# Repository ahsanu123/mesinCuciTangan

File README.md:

# Projek Dadakan - Mesin Cuci Tangan

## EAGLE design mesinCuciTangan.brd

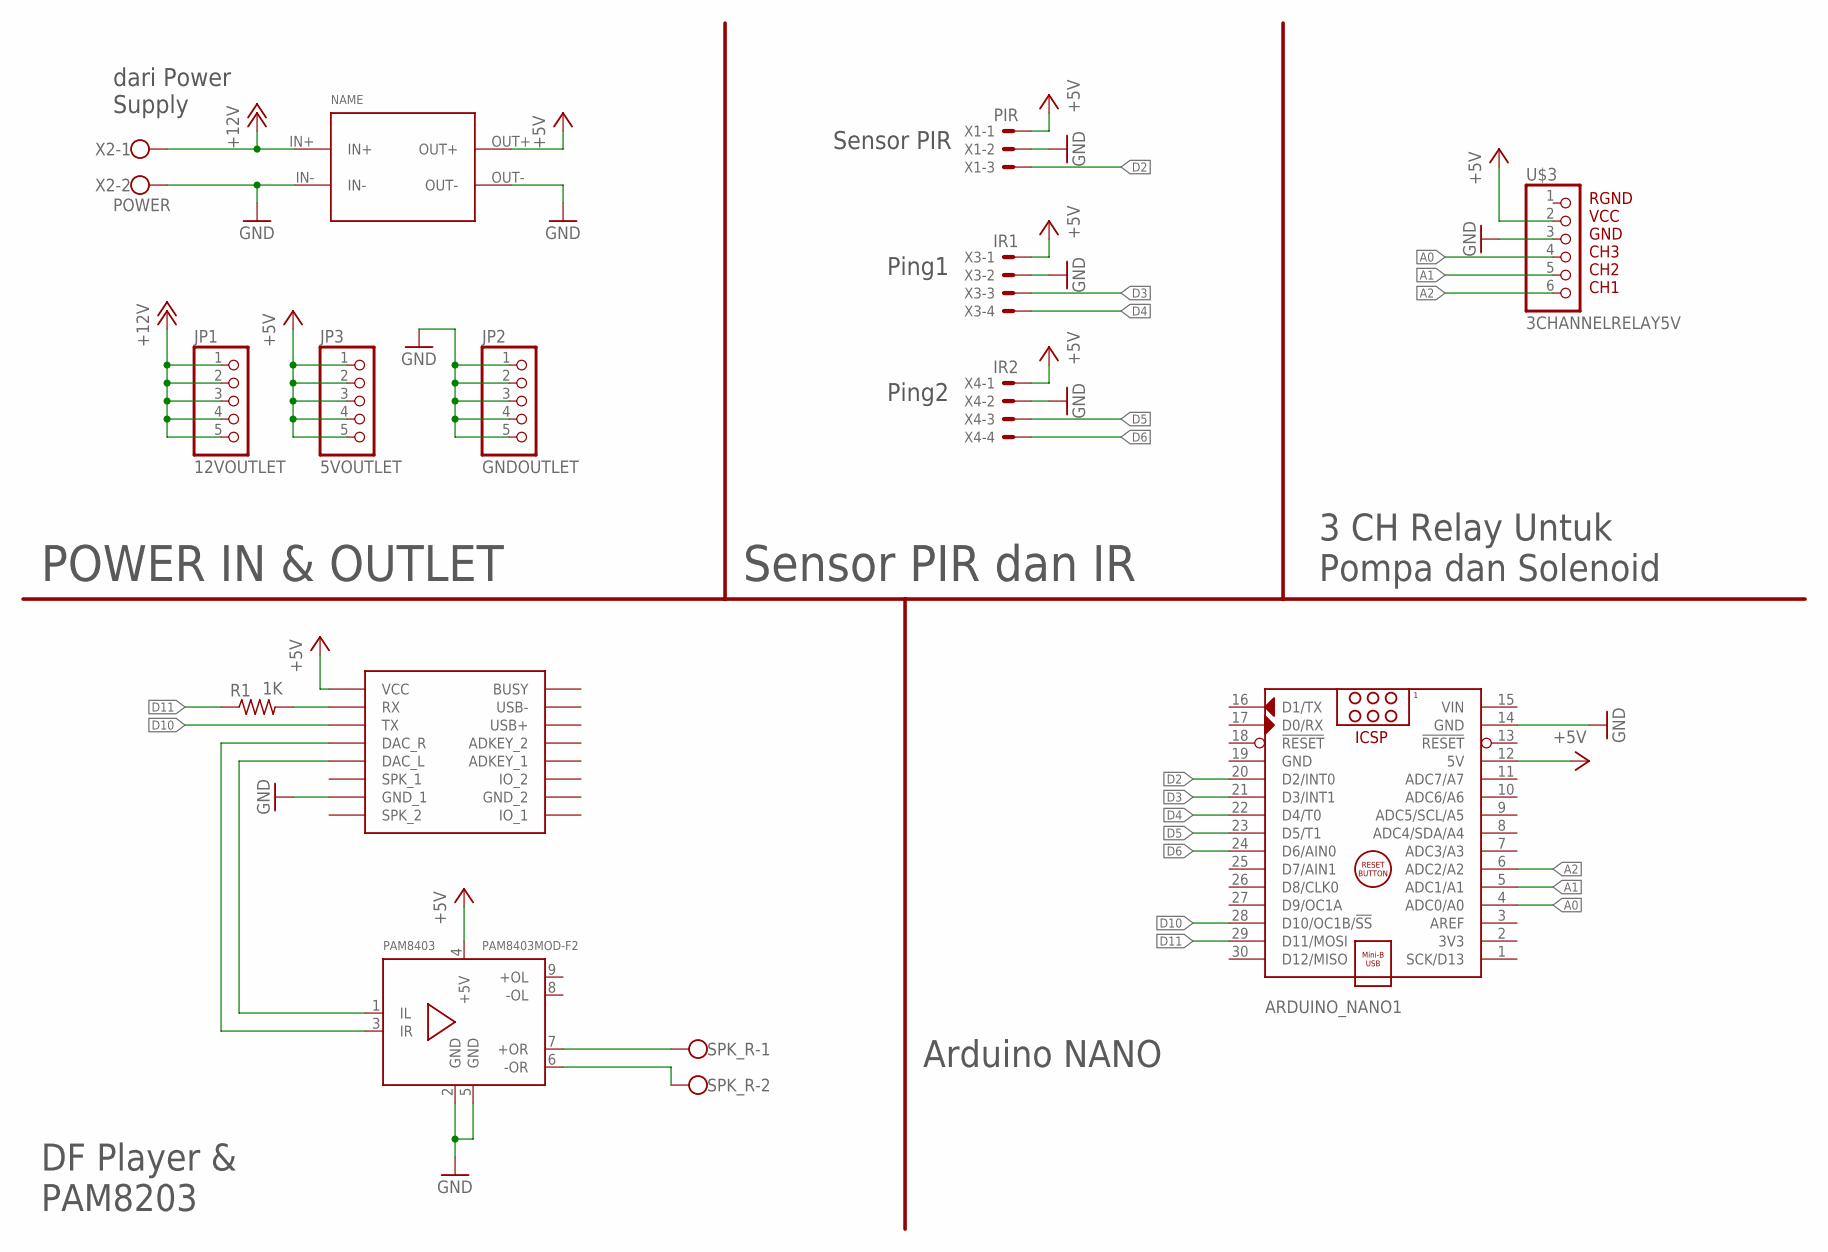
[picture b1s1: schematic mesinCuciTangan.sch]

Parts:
ARDUINO_NANO1: ARDUINO_NANO
JP1: 12VOUTLET; 1X05
JP2: GNDOUTLET; 1X05
JP3: 5VOUTLET; 1X05
LM2596: LM2596; CP8-ADJ
PAM8403: PAM8403MOD-F2; PAM8403MOD2
R1: 1K; 0207/10
SPK_R: W237-102
U$2: DFPLAYER
U$3: 3CHANNELRELAY5V; 3CHANNELRELAY
X1: PIR; 22-23-2031
X2: POWER; W237-102
X3: IR1; 22-23-2041
X4: IR2; 22-23-2041

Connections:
+5V: ARDUINO_NANO1.12 (5V), JP3.1, JP3.2, JP3.3, JP3.4, JP3.5, LM2596.OUT+, PAM8403.4 (+5V), U$2.VCC, U$3.2, X1.1, X3.1, X4.1
+12V: JP1.1, JP1.2, JP1.3, JP1.4, JP1.5, LM2596.IN+, X2.1
A0: ARDUINO_NANO1.4 (ADC0/A0), U$3.4
A1: ARDUINO_NANO1.5 (ADC1/A1), U$3.5
A2: ARDUINO_NANO1.6 (ADC2/A2), U$3.6
D2: ARDUINO_NANO1.20 (D2/INT0), X1.3
D3: ARDUINO_NANO1.21 (D3/INT1), X3.3
D4: ARDUINO_NANO1.22 (D4/T0), X3.4
D5: ARDUINO_NANO1.23 (D5/T1), X4.3
D6: ARDUINO_NANO1.24 (D6/AIN0), X4.4
D10: ARDUINO_NANO1.28 (D10/OC1B/!SS), U$2.TX
D11: ARDUINO_NANO1.29 (D11/MOSI), R1.1
GND: ARDUINO_NANO1.14 (GND), ARDUINO_NANO1.19 (GND), JP2.1, JP2.2, JP2.3, JP2.4, JP2.5, LM2596.IN-, LM2596.OUT-, PAM8403.2 (GND), PAM8403.5 (GND), U$2.GND_1, U$3.3, X1.2, X2.2, X3.2, X4.2
unnamed: PAM8403.7 (+OR), SPK_R.1
unnamed: PAM8403.1 (IL), U$2.DAC_L
unnamed: PAM8403.3 (IR), U$2.DAC_R
unnamed: PAM8403.6 (-OR), SPK_R.2
unnamed: R1.2, U$2.RX
VIN: ARDUINO_NANO1.15 (VIN)

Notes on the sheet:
dari Power Supply
Sensor PIR
Ping1
Ping2
POWER IN & OUTLET
Sensor PIR dan IR
3 CH Relay Untuk Pompa dan Solenoid
DF Player & PAM8203
Arduino NANO

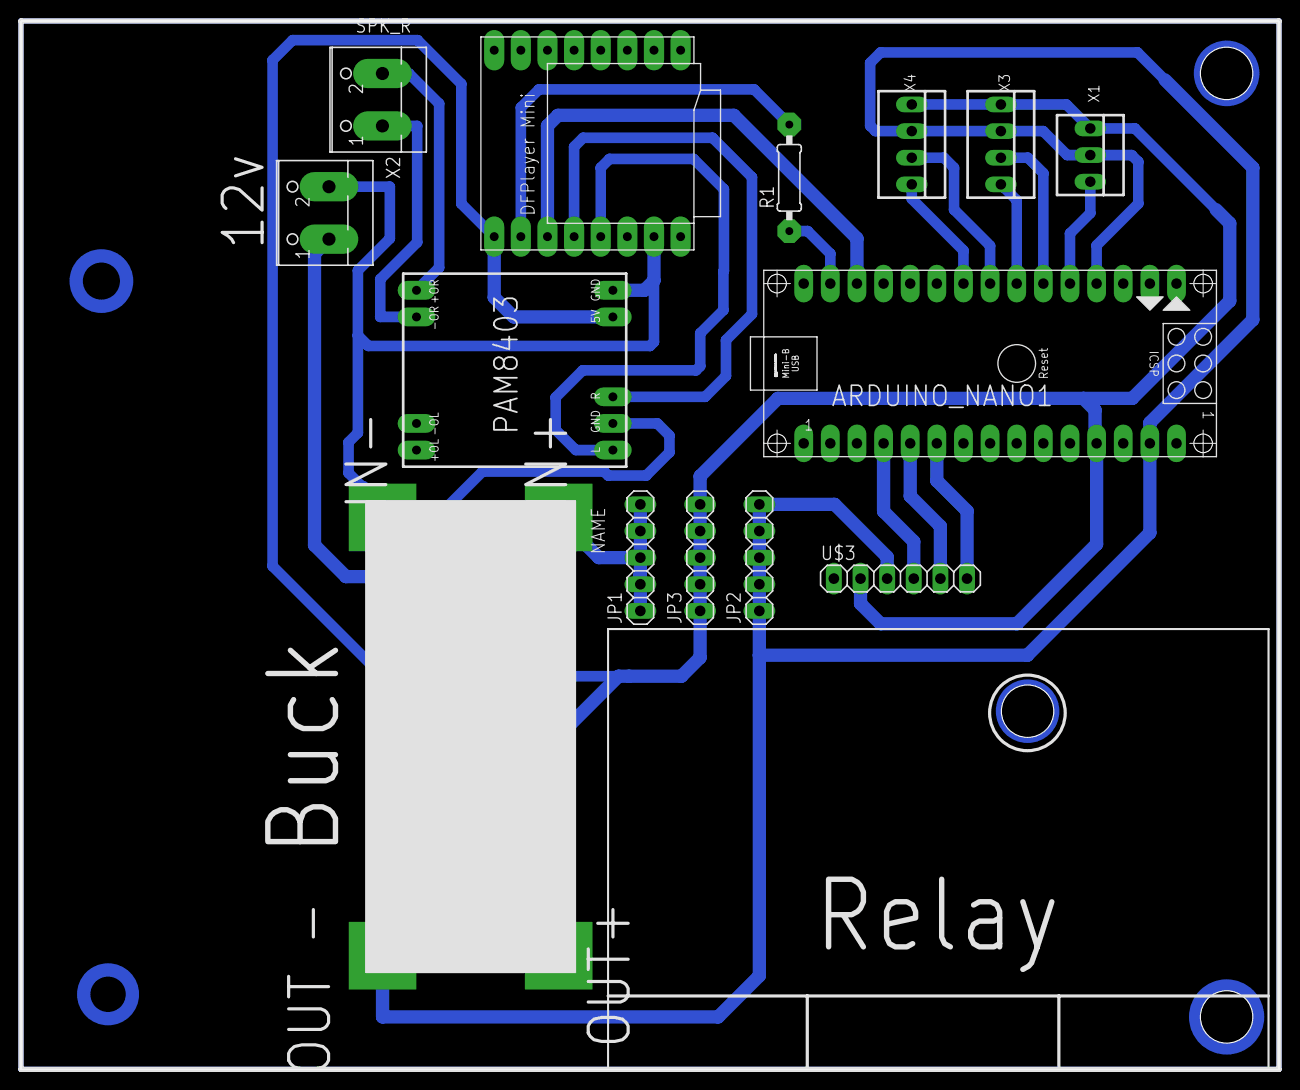
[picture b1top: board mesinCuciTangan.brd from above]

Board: 2 copper layers, 120.0 x 100.0 mm, 14 parts (0 on the bottom side), 18 nets.

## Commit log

2023-03-11 upload ke repo remote
2023-03-11 Skema Beta V0.1
2023-03-12 simple Route Without jumper
2023-03-13 update siap cetak 1
2023-03-13 pcb coba ceta #1
2023-05-15 commit with code
